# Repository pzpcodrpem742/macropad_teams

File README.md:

# macropad_teams
Code for a macropad that can be used on any Mac or Windows with Microsoft Teams

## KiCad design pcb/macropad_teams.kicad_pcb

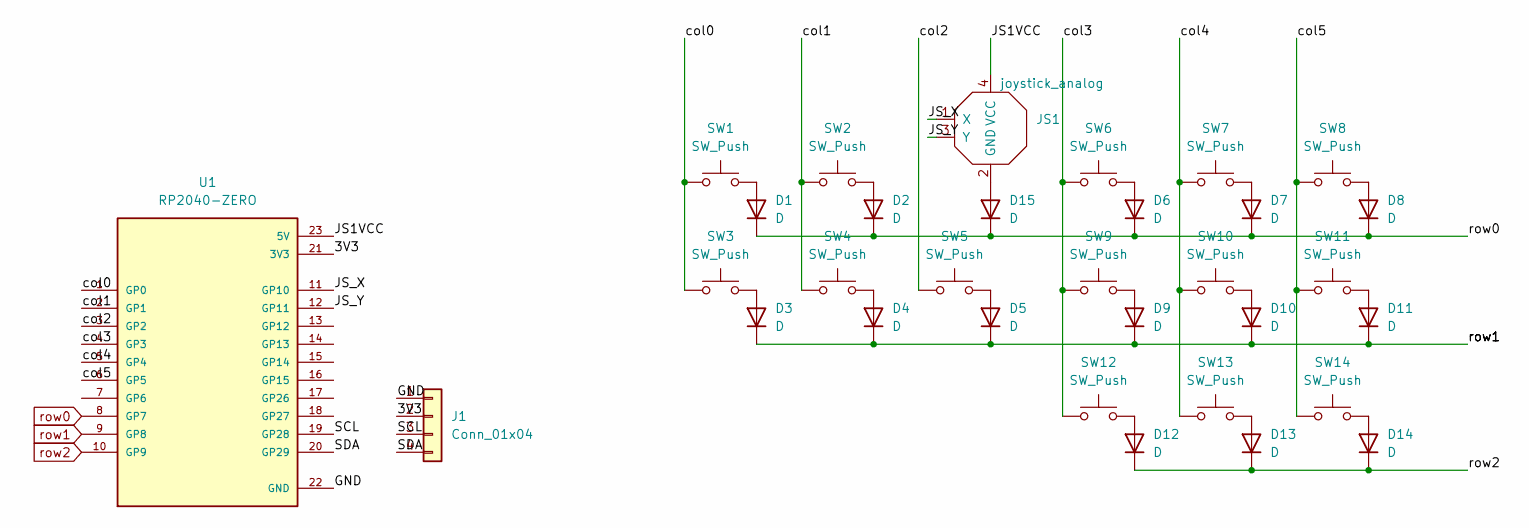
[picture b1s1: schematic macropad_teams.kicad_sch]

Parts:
D1, D2, D3, D4, D5, D6, D7, D8, D9, D10, D11, D12, D13, D14, D15: D; D_DO-35_SOD27_P7.62mm_Horizontal
J1: Conn_01x04; PinHeader_1x04_P2.54mm_Horizontal
JS1: joystick_analog; SW_SKRHABE010_SMD
SW1, SW2, SW3, SW4, SW5, SW6, SW7, SW8, SW9, SW10, SW11, SW12, SW13, SW14: SW_Push; SW_Cherry_MX_1.00u_PCB
U1: RP2040-ZERO; MODULE_RP2040-ZERO; PARTREV NA

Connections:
/3V3: J1.2, U1.21 (3V3)
/GND: J1.1, U1.22 (GND)
/JS1VCC: JS1.4 (VCC), U1.23 (5V)
/JS_X: JS1.1 (X), U1.11 (GP10)
/JS_Y: JS1.3 (Y), U1.12 (GP11)
/SCL: J1.3, U1.19 (GP28)
/SDA: J1.4, U1.20 (GP29)
/col0: SW1.1, SW3.1, U1.1 (GP0)
/col1: SW2.1, SW4.1, U1.2 (GP1)
/col2: SW5.1, U1.3 (GP2)
/col3: SW6.1, SW9.1, SW12.1, U1.4 (GP3)
/col4: SW7.1, SW10.1, SW13.1, U1.5 (GP4)
/col5: SW8.1, SW11.1, SW14.1, U1.6 (GP5)
unnamed: D1.2 (A), SW1.2
unnamed: D2.2 (A), SW2.2
unnamed: D3.2 (A), SW3.2
unnamed: D4.2 (A), SW4.2
unnamed: D5.2 (A), SW5.2
unnamed: D6.2 (A), SW6.2
unnamed: D7.2 (A), SW7.2
unnamed: D8.2 (A), SW8.2
unnamed: D9.2 (A), SW9.2
unnamed: D10.2 (A), SW10.2
unnamed: D11.2 (A), SW11.2
unnamed: D12.2 (A), SW12.2
unnamed: D13.2 (A), SW13.2
unnamed: D14.2 (A), SW14.2
unnamed: D15.2 (A), JS1.2 (GND)
row0: D1.1 (K), D2.1 (K), D6.1 (K), D7.1 (K), D8.1 (K), D15.1 (K), U1.8 (GP7)
row1: D3.1 (K), D4.1 (K), D5.1 (K), D9.1 (K), D10.1 (K), D11.1 (K), U1.9 (GP8)
row2: D12.1 (K), D13.1 (K), D14.1 (K), U1.10 (GP9)

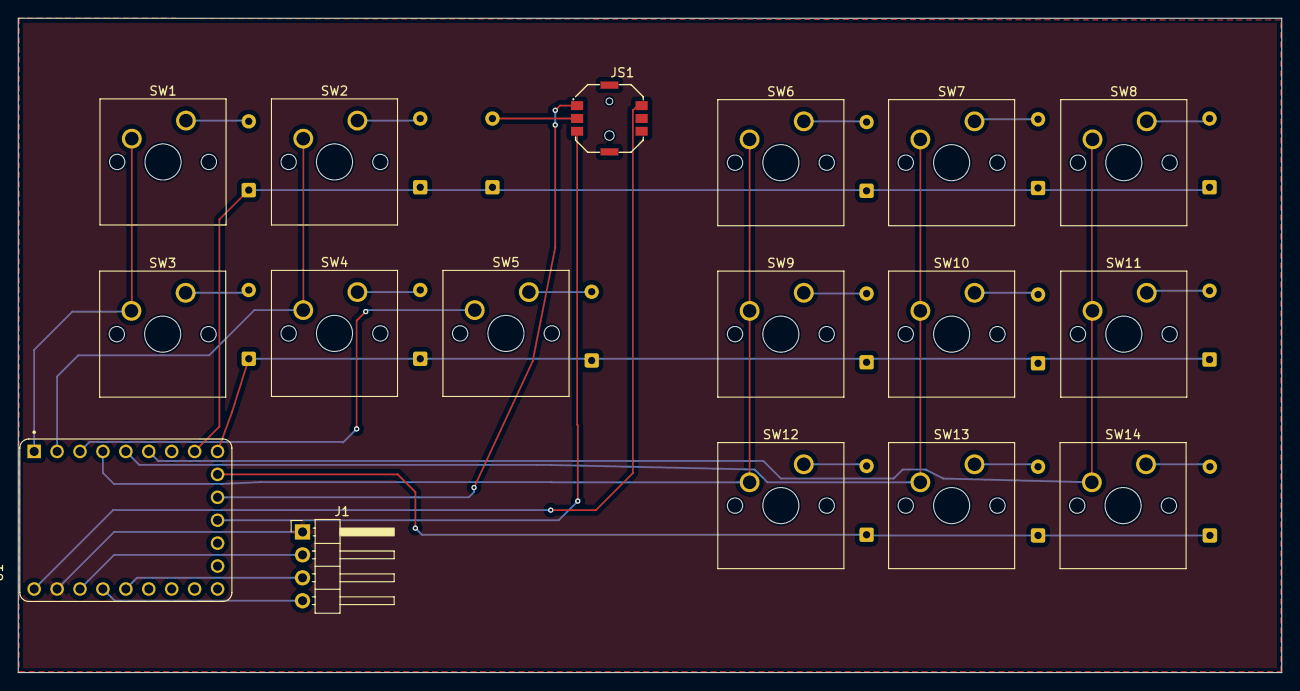
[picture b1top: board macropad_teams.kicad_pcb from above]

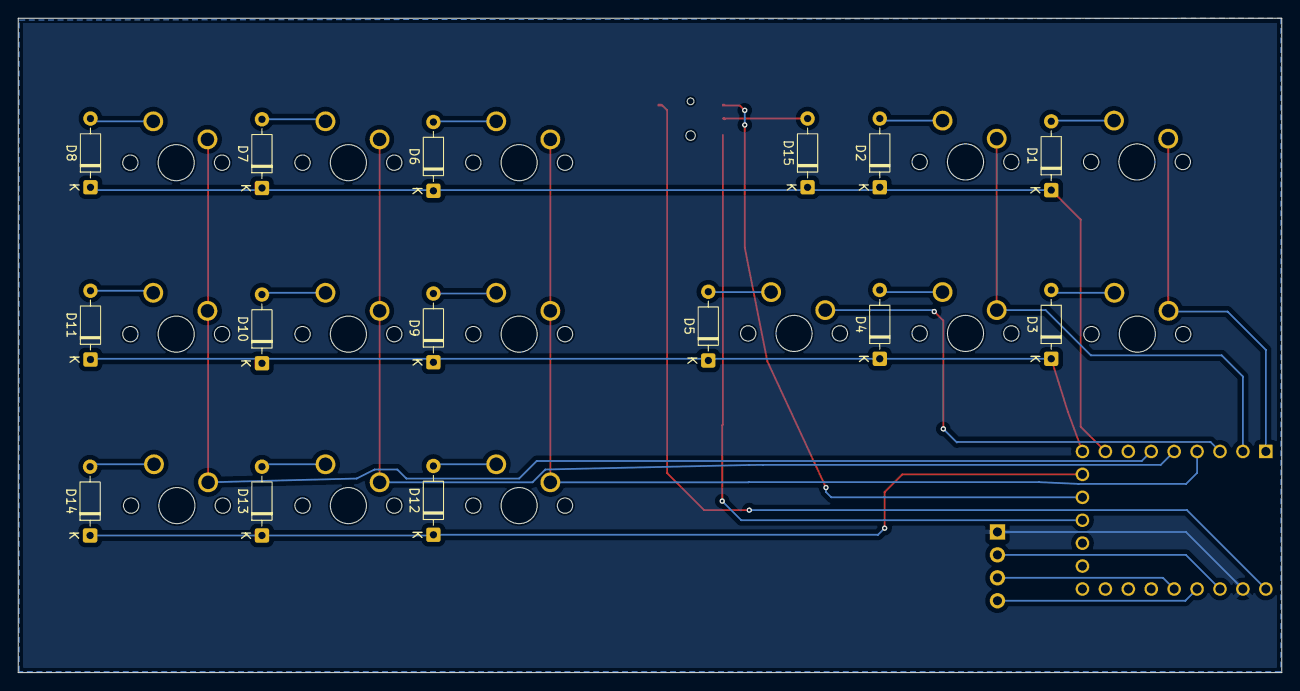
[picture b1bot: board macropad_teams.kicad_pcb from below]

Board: 2 copper layers, 140.0 x 72.5 mm, 32 parts (15 on the bottom side), 31 nets.

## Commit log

2025-11-06 The work done so far on macropad KiCad project
2025-11-06 On branch main Changes to be committed: deleted: pcb/macropad_teams-backups/macropad_teams-2025-09-16_111703.zip deleted: pcb/macropad_teams-backups/macropad_teams-2025-09-16_113002.zip deleted: pcb/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
2025-11-09 On branch main Changes to be committed: deleted: pcb/macropad_teams-backups/macropad_teams-2025-10-22_212323.zip deleted: pcb/macropad_teams-backups/macropad_teams-2025-10-22_213140.zip deleted: pcb/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
2025-11-09 On branch main Changes to be committed: deleted: pcb/macropad_teams-backups/macropad_teams-2025-10-26_193725.zip deleted: pcb/macropad_teams-backups/macropad_teams-2025-10-26_194634.zip modified: pcb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
2025-11-11 On branch main Changes to be committed: deleted: pcb/macropad_teams-backups/macropad_teams-2025-10-26_201154.zip deleted: pcb/macropad_teams-backups/macropad_teams-2025-10-26_203901.zip deleted: pcb/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
    Much neater PCB routing this time around
2025-11-11 On branch main Changes to be committed: deleted: pcb/macropad_teams-backups/macropad_teams-2025-10-28_144739.zip modified: pcb/macropad_teams.kicad_pcb
2025-11-11 modified: pcb/macropad_teams.kicad_prl
2025-11-11 On branch main Changes to be committed: deleted: pcb/macropad_teams-backups/macropad_teams-2025-10-28_145826.zip modified: pcb/macropad_teams.kicad_pcb
2025-11-13 On branch main Changes to be committed: deleted: pcb/macropad_teams-backups/macropad_teams-2025-10-28_200539.zip deleted: pcb/macropad_teams-backups/macropad_teams-2025-10-28_201254.zip deleted: pcb/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
    Successfully connected all parts of the joystick to the other components, whereas before this commit, there was an unrouted net.
2025-11-16 modified: .DS_Store new file: firmware/.DS_Store modified: pcb/.DS_Store modified: pcb/fp-info-cache new file: pcb/macropad_teams copy.kicad_sch deleted: pcb/macropad_teams-backups/macropad_teams-202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
2025-11-16 Changes to be committed: modified: .DS_Store modified: pcb/.DS_Store deleted: pcb/macropad_teams copy.kicad_sch deleted: pcb/macropad_teams-backups/macropad_teams-2025-11-01_175649.zip modified: pcb/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

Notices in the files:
parts and their libraries:
License: Apache-2.0
